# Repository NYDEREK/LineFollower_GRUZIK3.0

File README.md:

<h1 align="center">GRUZIK3.0: Line Follower Robot</h1>

<div align="center">

<i>Loved the project? Please consider giving a Star ⭐️</i>

</div>

> **GRUZIK2.0 is a lightweight construction (69g) designed for the "Line Follower Light" competition. The robot features Bluetooth communication with a smartphone app and uses a digital sensor instead of analog.**

> **here is a quick video of current progres with GRUZIK3.0 - https://www.youtube.com/watch?v=DpuIcFJMwbQ**
<div align="center">
  
</div>

## Hardware

> **The simple lightweight construction (69g) allows the robot to achieve high speed on the track.**
> **PCBs were designed in KiCAD 8.0 and manufactured by JLCPCB. The rims were 3D printed with PLA for Kyosho "Mini Z" tires.**
> **The light dualsky 150mAh battery provides enough current (max 30C) without adding too much weight (10g).**
> **The Pololu 2211 motor (10:1) with max current 1.6A per one requires the use of two separate TB6612FNG motor drivers with connected channels (max 2A per driver).**
> **The HC-05 Bluetooth module gives communication range up to 10m.**
> **The fast ARM microcontroller STM32G474RET6 (max 170MHz) provides a lot of software capabilities.**

- uC - STM32G474RET6
- drivers - TB6612FNG
- sensor - 12x KTIR0711S
- battery - 150mAh LiPo dualsky
- wheels - Kyosho Mini Z
- motors - Pololu 3071 HPCB
- Bluetooth - HC-04
- Encoders - AMS AS5047P-ATSM
- IMU - MPU-6050

## 🗺️ Mapping 🗺️
> **GRUZIK3.0 is able to record it's route and save it on uSD card. Results can be represented as XY map and optimized by Python algorithm, robot is able to recreate optimized map in real world achieving max speed for the given route**

<div align="center">

</div>

## 📱Bluetooth Apps 📱

> **Thease are simple Bluetooth apps created with MIT App Inventor. Spps start and stop the robot. The Modes pad is responsible for quickly adapting the speed and accuracy of the robot to the route using modes, and the application also displays the battery charge status. Second app is mainly for tweaking PID settings it allows you to change any parameter in seconds**

<div align="center">

</div>

## What I have learned 
> **This project wasn't easy but I learned a lot new things in software and hardware. I had a lot of failures during this project but I have never gave up and always kept pushing my own limits.**

- I mastered PID controll
 
- IMU implemantation 
 
- Encoder implementation with PI speed regulator on motors
 
- Mapping and optimizing Paths

- Improved my PCB design skills (KiCAD)

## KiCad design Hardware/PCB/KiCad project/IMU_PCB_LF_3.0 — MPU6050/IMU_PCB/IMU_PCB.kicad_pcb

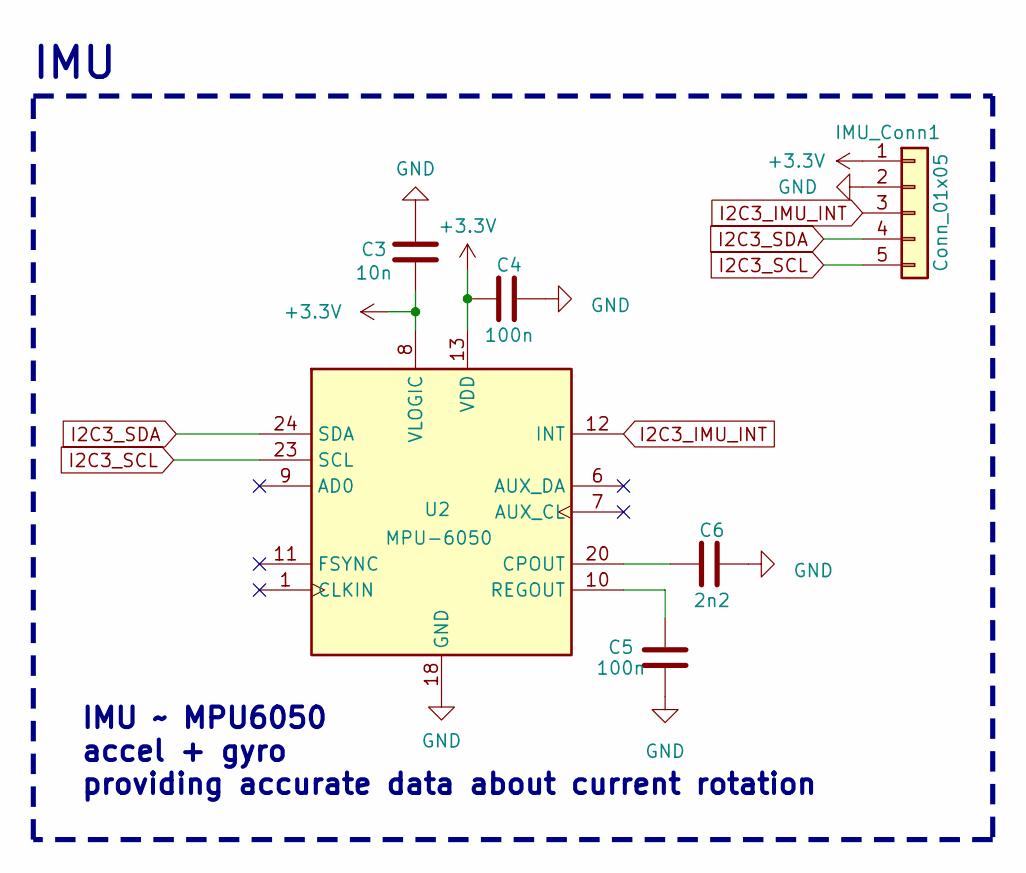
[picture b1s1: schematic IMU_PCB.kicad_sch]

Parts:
C3: 10n; C_0603_1608Metric
C4, C5: 100n; C_0603_1608Metric
C6: 2n2; C_0603_1608Metric
IMU_Conn1: Conn_01x05; IMU_conn
U2: MPU-6050; InvenSense_QFN-24_4x4mm_P0.5mm

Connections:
+3.3V: C3.1, C4.2, IMU_Conn1.1, U2.8 (VLOGIC), U2.13 (VDD)
GND: C3.2, C4.1, C5.2, C6.1, IMU_Conn1.2, U2.18 (GND)
I2C3_IMU_INT: IMU_Conn1.3, U2.12 (INT)
I2C3_SCL: IMU_Conn1.5, U2.23 (SCL)
I2C3_SDA: IMU_Conn1.4, U2.24 (SDA)
unnamed: C6.2, U2.20 (CPOUT)
unnamed: C5.1, U2.10 (REGOUT)

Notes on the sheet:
IMU
IMU ~ MPU6050 accel + gyro providing accurate data about current rotation

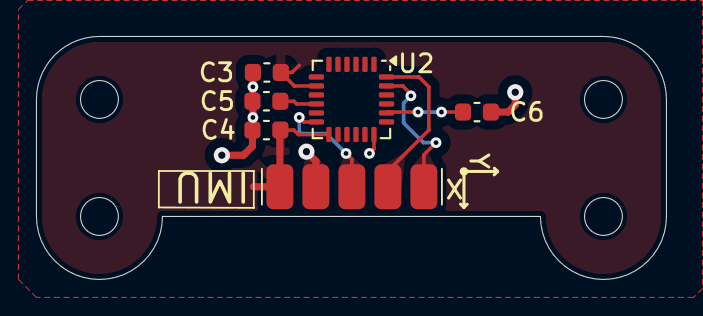
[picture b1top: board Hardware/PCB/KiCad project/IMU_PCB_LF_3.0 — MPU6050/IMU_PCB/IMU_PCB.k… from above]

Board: 2 copper layers, 35.0 x 13.5 mm, 6 parts (0 on the bottom side), 7 nets.

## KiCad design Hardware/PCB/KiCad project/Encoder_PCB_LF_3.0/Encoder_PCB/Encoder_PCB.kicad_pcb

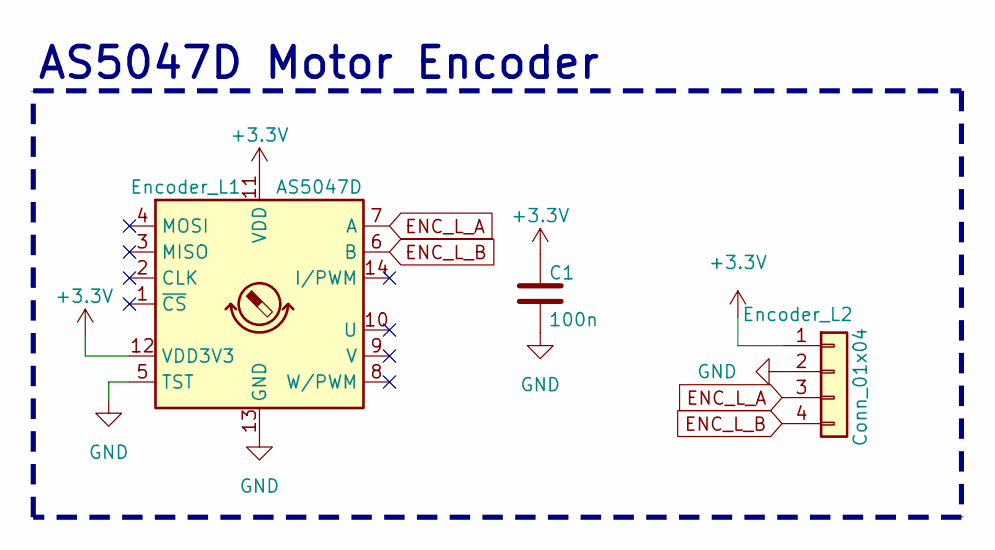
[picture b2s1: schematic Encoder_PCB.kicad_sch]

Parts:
C1: 100n; C_0603_1608Metric
Encoder_L1: AS5047D; TSSOP-14_4.4x5mm_P0.65mm
Encoder_L2: Conn_01x04; Encoder_short_conn

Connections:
+3.3V: C1.1, Encoder_L1.11 (VDD), Encoder_L1.12 (VDD3V3), Encoder_L2.1
ENC_L_A: Encoder_L1.7 (A), Encoder_L2.3
ENC_L_B: Encoder_L1.6 (B), Encoder_L2.4
GND: C1.2, Encoder_L1.5 (TST), Encoder_L1.13 (GND), Encoder_L2.2

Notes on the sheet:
AS5047D Motor Encoder

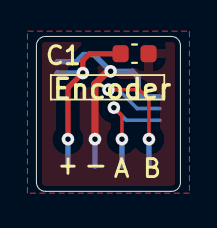
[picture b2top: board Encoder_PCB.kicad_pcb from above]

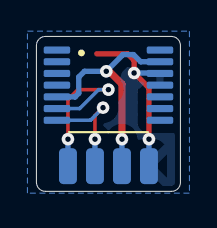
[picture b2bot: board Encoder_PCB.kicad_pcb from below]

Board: 2 copper layers, 8.0 x 8.6 mm, 3 parts (2 on the bottom side), 4 nets.

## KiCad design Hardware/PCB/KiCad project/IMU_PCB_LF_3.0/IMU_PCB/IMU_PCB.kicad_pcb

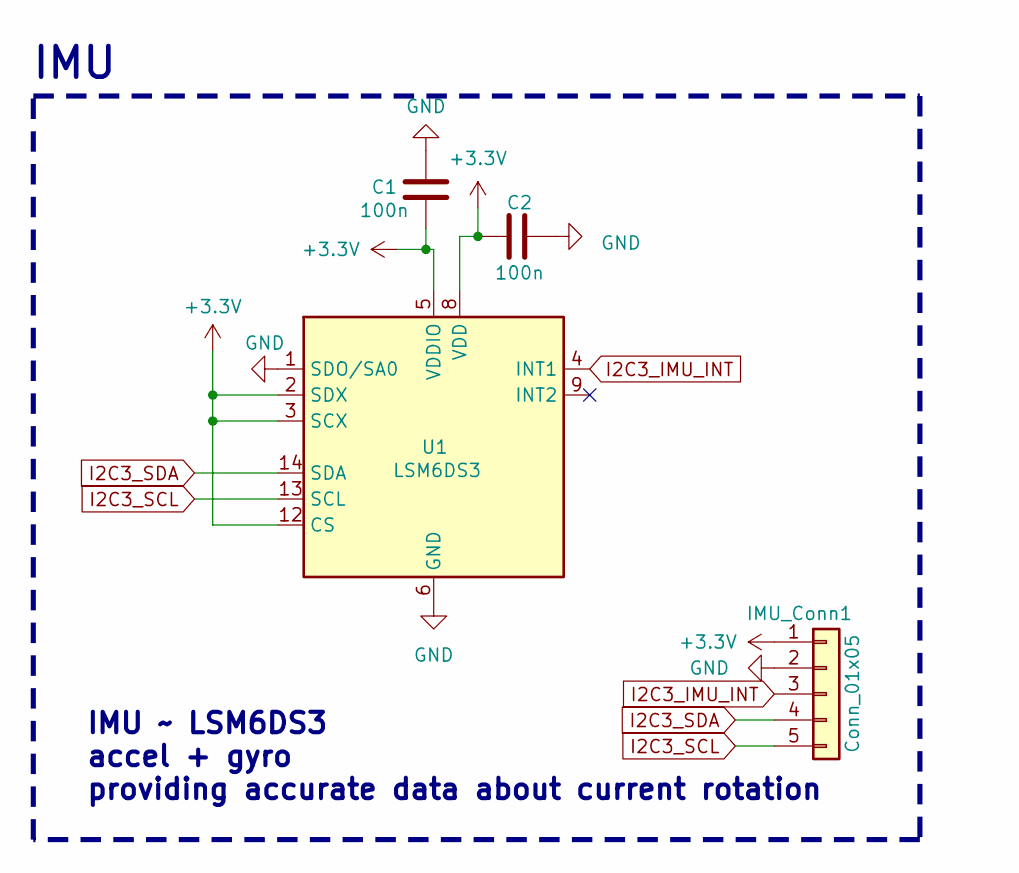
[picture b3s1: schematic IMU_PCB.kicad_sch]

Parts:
C1, C2: 100n; C_0603_1608Metric
IMU_Conn1: Conn_01x05; IMU_conn
U1: LSM6DS3; LGA-14_3x2.5mm_P0.5mm_LayoutBorder3x4y

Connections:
+3.3V: C1.1, C2.2, IMU_Conn1.1, U1.2 (SDX), U1.3 (SCX), U1.5 (VDDIO), U1.8 (VDD), U1.12 (CS)
GND: C1.2, C2.1, IMU_Conn1.2, U1.1 (SDO/SA0), U1.6 (GND), U1.7 (GND)
I2C3_IMU_INT: IMU_Conn1.3, U1.4 (INT1)
I2C3_SCL: IMU_Conn1.5, U1.13 (SCL)
I2C3_SDA: IMU_Conn1.4, U1.14 (SDA)

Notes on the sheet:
IMU ~ LSM6DS3 accel + gyro providing accurate data about current rotation
IMU

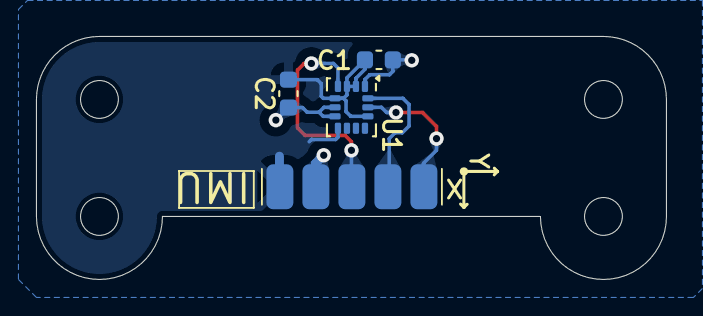
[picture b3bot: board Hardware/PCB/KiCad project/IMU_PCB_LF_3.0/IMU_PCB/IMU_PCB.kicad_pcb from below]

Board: 2 copper layers, 35.0 x 13.5 mm, 4 parts (4 on the bottom side), 5 nets.

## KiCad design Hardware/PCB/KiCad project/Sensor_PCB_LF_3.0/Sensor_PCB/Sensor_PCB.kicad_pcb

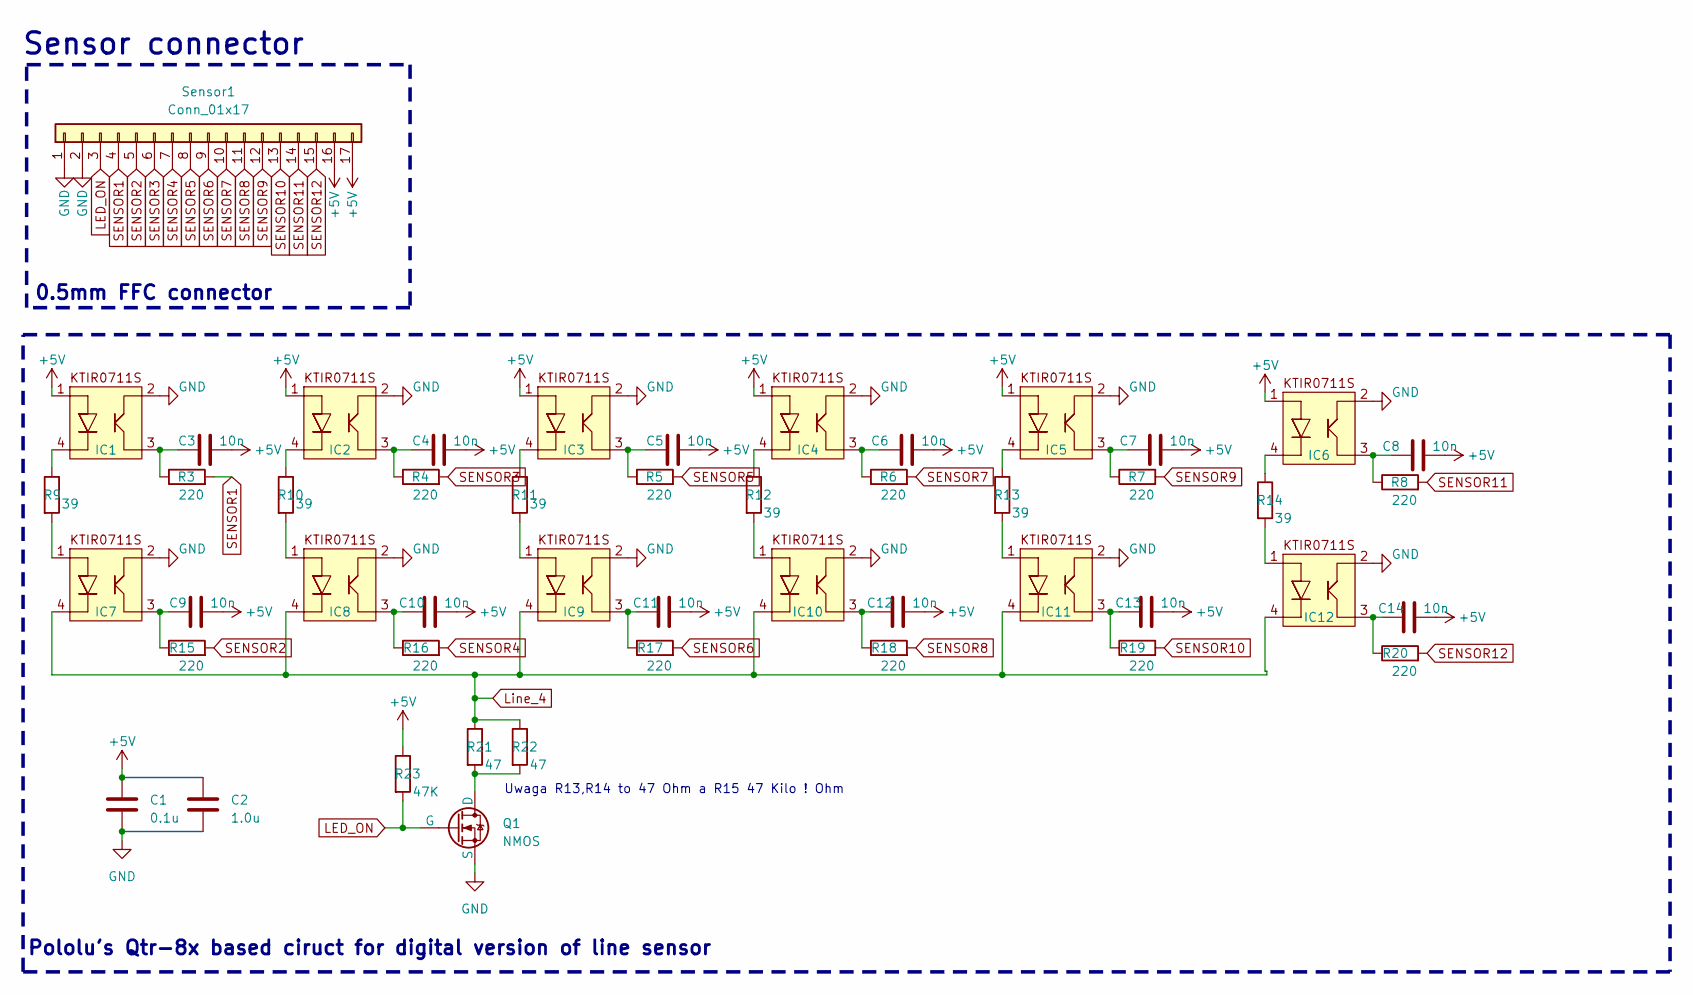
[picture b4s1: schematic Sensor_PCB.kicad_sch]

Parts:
C1: 0.1u; C_0603_1608Metric
C2: 1.0u; C_0603_1608Metric
C3, C4, C5, C6, C7, C8, C9, C10, C11, C12, C13, C14: 10n; C_0603_1608Metric
IC1, IC2, IC3, IC4, IC5, IC6, IC7, IC8, IC9, IC10, IC11, IC12: KTIR0711S
Q1: NMOS; NMOS_SN
R3, R4, R5, R6, R7, R8, R15, R16, R17, R18, R19, R20: 220; R_0603_1608Metric
R9, R10, R11, R12, R13, R14: 39; R_0603_1608Metric
R21, R22: 47; R_0603_1608Metric
R23: 47K; R_0603_1608Metric
Sensor1: Conn_01x17; Hirose_FH12-17S-0.5SH_1x17-1MP_P0.50mm_Horizontal

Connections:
+5V: C1.1, C2.1, C3.2, C4.2, C5.2, C6.2, C7.2, C8.2, C9.2, C10.2, C11.2, C12.2, C13.2, C14.2, IC1.1, IC2.1, IC3.1, IC4.1, IC5.1, IC6.1, R23.1, Sensor1.16, Sensor1.17; also elsewhere on the board
GND: C1.2, C2.2, IC1.2, IC2.2, IC3.2, IC4.2, IC5.2, IC6.2, IC7.2, IC8.2, IC9.2, IC10.2, IC11.2, IC12.2, Q1.3 (S), Sensor1.1, Sensor1.2; also elsewhere on the board
LED_ON: Q1.2 (G), R23.2, Sensor1.3; also elsewhere on the board
Line_4: IC7.4, IC8.4, IC9.4, IC10.4, IC11.4, IC12.4, R21.1, R22.1
unnamed: C3.1, IC1.3, R3.1
unnamed: C4.1, IC2.3, R4.1
unnamed: C5.1, IC3.3, R5.1
unnamed: C6.1, IC4.3, R6.1
unnamed: C7.1, IC5.3, R7.1
unnamed: C8.1, IC6.3, R8.1
unnamed: C9.1, IC7.3, R15.1
unnamed: C10.1, IC8.3, R16.1
unnamed: C11.1, IC9.3, R17.1
unnamed: C12.1, IC10.3, R18.1
unnamed: C13.1, IC11.3, R19.1
unnamed: C14.1, IC12.3, R20.1
unnamed: IC1.4, R9.1
unnamed: IC2.4, R10.1
unnamed: IC3.4, R11.1
unnamed: IC4.4, R12.1
unnamed: IC5.4, R13.1
unnamed: IC6.4, R14.1
unnamed: IC7.1, R9.2
unnamed: IC8.1, R10.2
unnamed: IC9.1, R11.2
unnamed: IC10.1, R12.2
unnamed: IC11.1, R13.2
unnamed: IC12.1, R14.2
unnamed: Q1.1 (D), R21.2, R22.2
SENSOR1: R3.2, Sensor1.4; also elsewhere on the board
SENSOR2: R15.2, Sensor1.5; also elsewhere on the board
SENSOR3: R4.2, Sensor1.6; also elsewhere on the board
SENSOR4: R16.2, Sensor1.7; also elsewhere on the board
SENSOR5: R5.2, Sensor1.8; also elsewhere on the board
SENSOR6: R17.2, Sensor1.9; also elsewhere on the board
SENSOR7: R6.2, Sensor1.10; also elsewhere on the board
SENSOR8: R18.2, Sensor1.11; also elsewhere on the board
SENSOR9: R7.2, Sensor1.12; also elsewhere on the board
SENSOR10: R19.2, Sensor1.13; also elsewhere on the board
SENSOR11: R8.2, Sensor1.14; also elsewhere on the board
SENSOR12: R20.2, Sensor1.15; also elsewhere on the board

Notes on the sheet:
Uwaga R13,R14 to 47 Ohm a R15 47 Kilo ! Ohm
Pololu's Qtr-8x based ciruct for digital version of line sensor
0.5mm FFC connector
Sensor connector

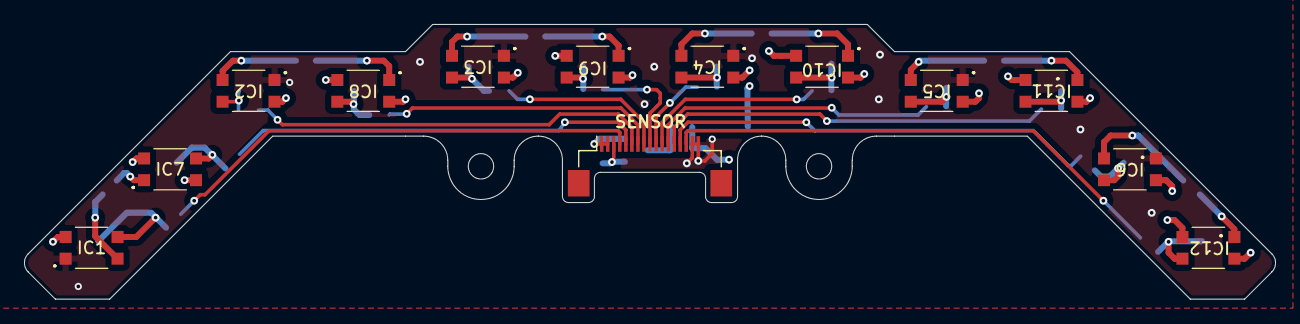
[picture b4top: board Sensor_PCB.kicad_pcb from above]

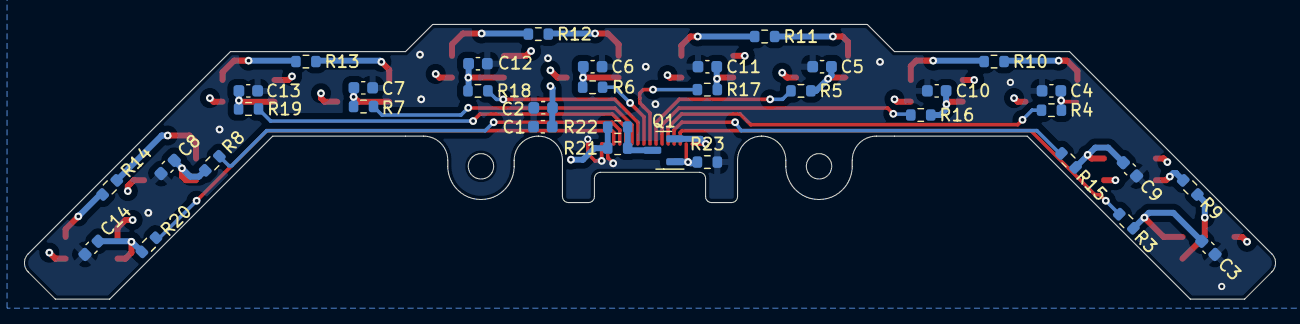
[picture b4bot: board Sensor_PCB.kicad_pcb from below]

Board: 4 copper layers, 103.6 x 22.8 mm, 49 parts (36 on the bottom side), 41 nets.

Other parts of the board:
SENSOR: Conn_01x17; Hirose_FH12-17S-0.5SH_1x17-1MP_P0.50mm_Horizontal

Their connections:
+5V: SENSOR.16, SENSOR.17; also elsewhere on the board
GND: SENSOR.1, SENSOR.2; also elsewhere on the board
LED_ON: SENSOR.3; also elsewhere on the board
SENSOR1: SENSOR.4; also elsewhere on the board
SENSOR2: SENSOR.5; also elsewhere on the board
SENSOR3: SENSOR.6; also elsewhere on the board
SENSOR4: SENSOR.7; also elsewhere on the board
SENSOR5: SENSOR.8; also elsewhere on the board
SENSOR6: SENSOR.9; also elsewhere on the board
SENSOR7: SENSOR.10; also elsewhere on the board
SENSOR8: SENSOR.11; also elsewhere on the board
SENSOR9: SENSOR.12; also elsewhere on the board
SENSOR10: SENSOR.13; also elsewhere on the board
SENSOR11: SENSOR.14; also elsewhere on the board
SENSOR12: SENSOR.15; also elsewhere on the board

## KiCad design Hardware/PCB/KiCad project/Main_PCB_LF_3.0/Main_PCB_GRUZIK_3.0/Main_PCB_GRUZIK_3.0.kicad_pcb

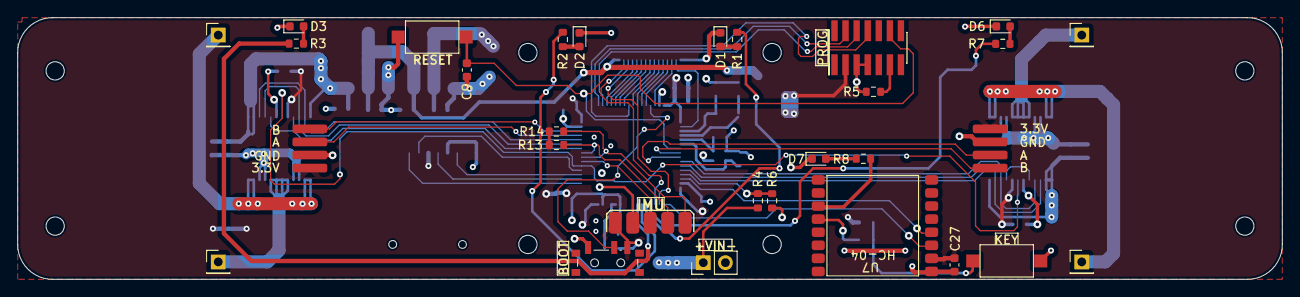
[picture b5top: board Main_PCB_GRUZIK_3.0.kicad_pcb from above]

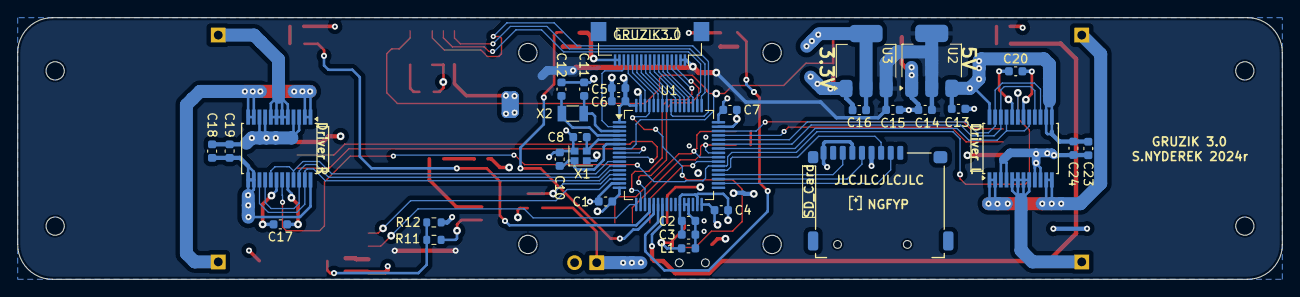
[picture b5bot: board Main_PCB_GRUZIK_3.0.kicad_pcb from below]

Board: 4 copper layers, 145.0 x 30.0 mm, 63 parts (33 on the bottom side), 65 nets.

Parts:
+VIN-: +VIN-; PinHeader_1x02_P2.54mm_Vertical
BOOT: SW_DPDT_x2; SW_SPDT_PCM12
C1, C2, C5, C6, C7, C9, C17, C18, C20, C23: 100n; C_0603_1608Metric
C3, C27: 1u; C_0603_1608Metric
C4: 4u7; C_0603_1608Metric
C8, C10: 6p8; C_0603_1608Metric
C11, C12: 5p1; C_0603_1608Metric
C13, C14, C15, C16, C19, C24: 10u; C_0603_1608Metric
D1, D2, D3, D6: BLUE; LED_0603_1608Metric
D7: Green; LED_0603_1608Metric
Driver L: TB6612FNG; SSOP-24_5.3x8.2mm_P0.65mm
Driver R: TB6612FNG; SSOP-24_5.3x8.2mm_P0.65mm
Encoder_L1, Encoder_L2: Conn_01x04; Encoder_short_conn
GRUZIK3.0: Conn_01x17; Hirose_FH12-17S-0.5SH_1x17-1MP_P0.50mm_Horizontal
IMU: Conn_01x05; IMU_conn
KEY: SW_SPST; SW_SPST_CK_RS282G05A3
L1: 27n; L_0603_1608Metric
P1, P2, P3, P4: Conn_01x01; PinHeader_1x01_P2.54mm_Vertical
PROG: Conn_02x07_Odd_Even; PinHeader_2x07_P1.27mm_Vertical_SMD
R1, R2, R3, R7: 510R; R_0603_1608Metric
R4: 330K; R_0603_1608Metric
R5: 100R; R_0603_1608Metric
R6: 200K; R_0603_1608Metric
R8: 510; R_0603_1608Metric
R11: 220; R_0603_1608Metric
R12, R13, R14: 10K; R_0603_1608Metric
RESET: SW_SPST; SW_SPST_CK_RS282G05A3
SD_Card: Micro_SD_Card; micro_SD
U1: STM32G474RETx; LQFP-64_10x10mm_P0.5mm
U2: AMS1117-5.0; SOT-223-3_TabPin2
U3: AMS1117-3.3; SOT-223-3_TabPin2
U7: HC-04
X1: 24Mhz; Crystal_SMD_2016-4Pin_2.0x1.6mm
X2: 32.768KHz; Crystal_SMD_3215-2Pin_3.2x1.5mm

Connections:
+3V3: BOOT.3 (C), C1.1, C4.1, C5.1, C6.1, C7.1, C16.1, C17.1, C20.1, C27.1, Driver L.20 (VCC), Driver R.20 (VCC), Encoder_L1.1, Encoder_L2.1, IMU.1, L1.2, PROG.3, R12.2, R13.1, R14.1, SD_Card.4 (VDD), U1.1 (VBAT), U1.16 (VDD), U1.32 (VDD), U1.48 (VDD), U1.64 (VDD), U3.2 (VO), U7.2 (3.3V)
+5V: C14.1, C15.1, GRUZIK3.0.1, GRUZIK3.0.2, U2.2 (VO), U3.3 (VI)
/HSE_IN: C8.2, U1.5 (PF0), X1.3
/HSE_OUT: C10.2, U1.6 (PF1), X1.1
/LSE_IN: C11.2, U1.3 (PC14), X2.2
/LSE_OUT: C12.2, U1.4 (PC15), X2.1
ADC_IN2: R4.1, R6.2, U1.13 (PA1)
BOOT0: BOOT.2 (B), U1.61 (PB8)
ENC_L_A: Encoder_L1.3, U1.45 (PA11)
ENC_L_B: Encoder_L1.4, U1.46 (PA12)
ENC_R_A: Encoder_L2.3, U1.9 (PC1)
ENC_R_B: Encoder_L2.4, U1.8 (PC0)
GND: +VIN-.2, BOOT.1 (A), C1.2, C2.2, C3.2, C4.2, C5.2, C6.2, C7.2, C8.1, C9.1, C10.1, C11.1, C12.1, C13.2, C14.2, C15.2, C16.2, C17.2, C18.2, C19.2, C20.2, C23.2, C24.2, C27.2, D1.1 (K), D2.1 (K), D3.1 (K), D6.1 (K), D7.1 (K), Driver L.3 (PGND1), Driver L.4 (PGND1), Driver L.9 (PGND2), Driver L.10 (PGND2), Driver L.18 (GND), Driver R.3 (PGND1), Driver R.4 (PGND1), Driver R.9 (PGND2), Driver R.10 (PGND2), Driver R.18 (GND), Encoder_L1.2, Encoder_L2.2, GRUZIK3.0.16, GRUZIK3.0.17, IMU.2, KEY.2 (B), PROG.5, PROG.7, R5.1, R6.1, RESET.1 (A), SD_Card.6 (VSS), SD_Card.9 (SHIELD), U1.15 (VSS), U1.27 (VSSA), U1.31 (VSS), U1.47 (VSS), U1.63 (VSS), U2.1 (GND), U3.1 (GND), U7.1 (GND), X1.2, X1.4
I2C3_IMU_INT: IMU.3, U1.39 (PC7)
I2C3_SCL: IMU.5, R14.2, U1.40 (PC8)
I2C3_SDA: IMU.4, R13.2, U1.41 (PC9)
LED_1: R3.2, U1.23 (PC5)
LED_2: R2.2, U1.22 (PC4)
LED_3: R1.2, U1.21 (PA7)
LED_4: R7.2, U1.20 (PA6)
LED_ON: GRUZIK3.0.15, U1.2 (PC13)
LPUART1_RX: U1.17 (PA3), U7.3 (Tx)
LPUART1_TX: U1.14 (PA2), U7.4 (Rx)
Motor_L_A: Driver L.17 (BIN1), Driver L.21 (AIN1), U1.42 (PA8)
Motor_L_B: Driver L.16 (BIN2), Driver L.22 (AIN2), U1.43 (PA9)
Motor_R_A: Driver R.17 (BIN1), Driver R.21 (AIN1), U1.10 (PC2)
Motor_R_B: Driver R.16 (BIN2), Driver R.22 (AIN2), U1.11 (PC3)
Motor_STBY: Driver L.19 (STBY), Driver R.19 (STBY), U1.38 (PC6)
NRST: C9.2, PROG.12, RESET.2 (B), U1.7 (PG10)
unnamed: D1.2 (A), R1.1
unnamed: D2.2 (A), R2.1
unnamed: D3.2 (A), R3.1
unnamed: D6.2 (A), R7.1
unnamed: D7.2 (A), R8.2
unnamed: KEY.1 (A), R11.2, R12.1
unnamed: Driver R.5 (AO2), Driver R.6 (AO2), Driver R.7 (BO2), Driver R.8 (BO2), P1.1
unnamed: Driver R.1 (AO1), Driver R.2 (AO1), Driver R.11 (BO1), Driver R.12 (BO1), P2.1
unnamed: Driver L.5 (AO2), Driver L.6 (AO2), Driver L.7 (BO2), Driver L.8 (BO2), P3.1
unnamed: Driver L.1 (AO1), Driver L.2 (AO1), Driver L.11 (BO1), Driver L.12 (BO1), P4.1
unnamed: PROG.11, R5.2
unnamed: R11.1, U7.12 (KEY)
unnamed: R8.1, U7.11 (LED)
PWM_L: Driver L.15 (PWMB), Driver L.23 (PWMA), U1.44 (PA10)
PWM_R: Driver R.15 (PWMB), Driver R.23 (PWMA), U1.12 (PA0)
SENSOR1: GRUZIK3.0.14, U1.62 (PB9)
SENSOR2: GRUZIK3.0.13, U1.60 (PB7)
SENSOR3: GRUZIK3.0.12, U1.59 (PB6)
SENSOR4: GRUZIK3.0.11, U1.58 (PB5)
SENSOR5: GRUZIK3.0.10, U1.57 (PB4)
SENSOR6: GRUZIK3.0.9, U1.55 (PD2)
SENSOR7: GRUZIK3.0.8, U1.54 (PC12)
SENSOR8: GRUZIK3.0.7, U1.53 (PC11)
SENSOR9: GRUZIK3.0.6, U1.52 (PC10)
SENSOR10: GRUZIK3.0.5, U1.51 (PA15)
SENSOR11: GRUZIK3.0.4, U1.18 (PA4)
SENSOR12: GRUZIK3.0.3, U1.19 (PA5)
SPI2_CLK: SD_Card.5 (CLK), U1.35 (PB13)
SPI2_CS: SD_Card.2 (DAT3/CD), U1.34 (PB12)
SPI2_MISO: SD_Card.7 (DAT0), U1.36 (PB14)
SPI2_MOSI: SD_Card.3 (CMD), U1.37 (PB15)
SYS_JTCK_SWCLK: PROG.6, U1.50 (PA14)
SYS_JTDO_SWO: PROG.8, U1.56 (PB3)
SYS_JTMS_SWDIO: PROG.4, U1.49 (PA13)
VDC: +VIN-.1, C13.1, C18.1, C19.1, C23.1, C24.1, Driver L.13 (VM2), Driver L.14 (VM3), Driver L.24 (VM1), Driver R.13 (VM2), Driver R.14 (VM3), Driver R.24 (VM1), R4.2, U2.3 (VI)
VREF+: C2.1, C3.1, L1.1, U1.28 (VREF+), U1.29 (VDDA)

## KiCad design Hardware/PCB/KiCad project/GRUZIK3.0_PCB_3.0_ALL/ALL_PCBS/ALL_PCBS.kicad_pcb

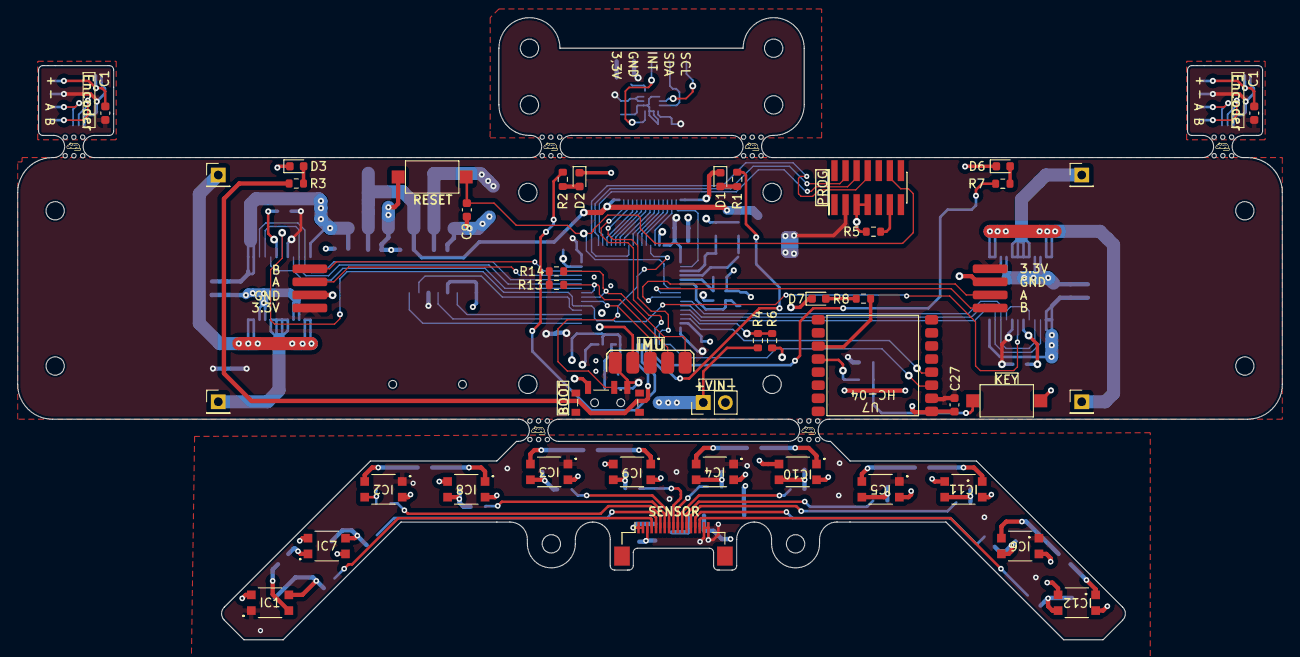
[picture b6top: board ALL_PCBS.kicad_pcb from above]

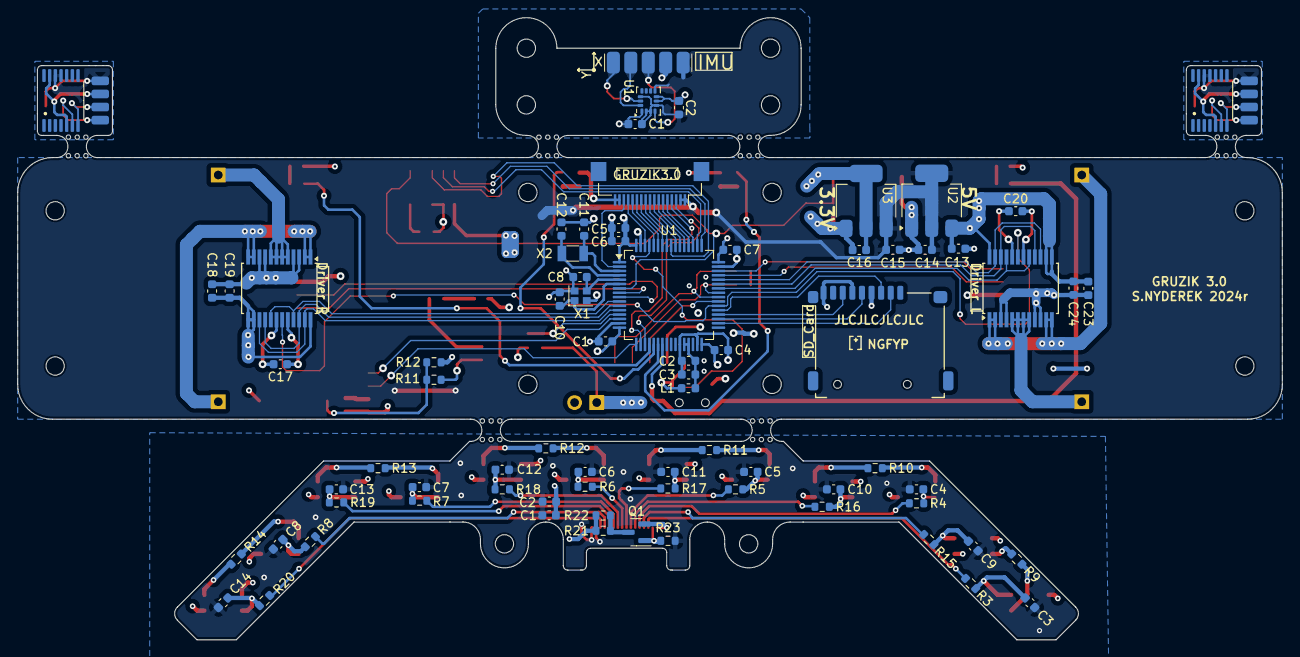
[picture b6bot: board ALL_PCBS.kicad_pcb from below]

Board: 4 copper layers, 145.0 x 71.3 mm, 128 parts (77 on the bottom side), 92 nets.

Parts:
+VIN-: +VIN-; PinHeader_1x02_P2.54mm_Vertical
BOOT: SW_DPDT_x2; SW_SPDT_PCM12
C1, C1#2, C1#3, C1#4, C2, C2#2, C5, C6#2, C7#2, C9, C17, C18, C20, C23: 100n; C_0603_1608Metric
C1#5: 0.1u; C_0603_1608Metric
C2#3: 1.0u; C_0603_1608Metric
C3, C27: 1u; C_0603_1608Metric
C3#2, C4, C5#2, C6, C7, C8, C9#2, C10#2, C11#2, C12, C13, C14: 10n; C_0603_1608Metric
C4#2: 4u7; C_0603_1608Metric
C8#2, C10: 6p8; C_0603_1608Metric
C11, C12#2: 5p1; C_0603_1608Metric
C13#2, C14#2, C15, C16, C19, C24: 10u; C_0603_1608Metric
D1, D2, D3, D6: BLUE; LED_0603_1608Metric
D7: Green; LED_0603_1608Metric
Driver L: TB6612FNG; SSOP-24_5.3x8.2mm_P0.65mm
Driver R: TB6612FNG; SSOP-24_5.3x8.2mm_P0.65mm
Encoder_L1, Encoder_L2, Encoder_L2#2, Encoder_L2#3: Conn_01x04; Encoder_short_conn
Encoder_L1#2, Encoder_L1#3: AS5047D; TSSOP-14_4.4x5mm_P0.65mm
GRUZIK3.0: Conn_01x17; Hirose_FH12-17S-0.5SH_1x17-1MP_P0.50mm_Horizontal
IC1, IC2, IC3, IC4, IC5, IC6, IC7, IC8, IC9, IC10, IC11, IC12: KTIR0711S
IMU: Conn_01x05; IMU_conn
IMU_Conn1: Conn_01x05; IMU_conn
KEY: SW_SPST; SW_SPST_CK_RS282G05A3
L1: 27n; L_0603_1608Metric
P1, P2, P3, P4: Conn_01x01; PinHeader_1x01_P2.54mm_Vertical
PROG: Conn_02x07_Odd_Even; PinHeader_2x07_P1.27mm_Vertical_SMD
Q1: NMOS; NMOS_SN
R1, R2, R3, R7: 510R; R_0603_1608Metric
R3#2, R4#2, R5#2, R6#2, R7#2, R8#2, R11#2, R15, R16, R17, R18, R19, R20: 220; R_0603_1608Metric
R4: 330K; R_0603_1608Metric
R5: 100R; R_0603_1608Metric
R6: 200K; R_0603_1608Metric
R8: 510; R_0603_1608Metric
R9, R10, R11, R12#2, R13#2, R14#2: 39; R_0603_1608Metric
R12, R13, R14: 10K; R_0603_1608Metric
R21, R22: 47; R_0603_1608Metric
R23: 47K; R_0603_1608Metric
RESET: SW_SPST; SW_SPST_CK_RS282G05A3
SD_Card: Micro_SD_Card; micro_SD
SENSOR: Conn_01x17; Hirose_FH12-17S-0.5SH_1x17-1MP_P0.50mm_Horizontal
U1: LSM6DS3; LGA-14_3x2.5mm_P0.5mm_LayoutBorder3x4y
U1#2: STM32G474RETx; LQFP-64_10x10mm_P0.5mm
U2: AMS1117-5.0; SOT-223-3_TabPin2
U3: AMS1117-3.3; SOT-223-3_TabPin2
U7: HC-04
X1: 24Mhz; Crystal_SMD_2016-4Pin_2.0x1.6mm
X2: 32.768KHz; Crystal_SMD_3215-2Pin_3.2x1.5mm
mouse-bite-2.54mm-4.66mm, mouse-bite-2.54mm-4.66mm#2, mouse-bite-2.54mm-4.66mm#3, mouse-bite-2.54mm-4.66mm#4, mouse-bite-2.54mm-4.66mm#5, mouse-bite-2.54mm-4.66mm#6: VAL**; mouse-bite-2.54mm-4.66mm

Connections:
+3.3V: C1.1, C1#2.1, C1#3.1, C2#2.2, Encoder_L1#2.11 (VDD), Encoder_L1#2.12 (VDD3V3), Encoder_L1#3.11 (VDD), Encoder_L1#3.12 (VDD3V3), Encoder_L2#2.1, Encoder_L2#3.1, IMU_Conn1.1, U1.2 (SDX), U1.3 (SCX), U1.5 (VDDIO), U1.8 (VDD), U1.12 (CS)
+3V3: BOOT.3 (C), C1#4.1, C4#2.1, C5.1, C6#2.1, C7#2.1, C16.1, C17.1, C20.1, C27.1, Driver L.20 (VCC), Driver R.20 (VCC), Encoder_L1.1, Encoder_L2.1, IMU.1, L1.2, PROG.3, R12.2, R13.1, R14.1, SD_Card.4 (VDD), U1#2.1 (VBAT), U1#2.16 (VDD), U1#2.32 (VDD), U1#2.48 (VDD), U1#2.64 (VDD), U3.2 (VO), U7.2 (3.3V)
+5V: C1#5.1, C2#3.1, C3#2.2, C4.2, C5#2.2, C6.2, C7.2, C8.2, C9#2.2, C10#2.2, C11#2.2, C12.2, C13.2, C14.2, C14#2.1, C15.1, GRUZIK3.0.1, GRUZIK3.0.2, IC1.1, IC2.1, IC3.1, IC4.1, IC5.1, IC6.1, R23.1, SENSOR.16, SENSOR.17, U2.2 (VO), U3.3 (VI)
/HSE_IN: C8#2.2, U1#2.5 (PF0), X1.3
/HSE_OUT: C10.2, U1#2.6 (PF1), X1.1
/LSE_IN: C11.2, U1#2.3 (PC14), X2.2
/LSE_OUT: C12#2.2, U1#2.4 (PC15), X2.1
ADC_IN2: R4.1, R6.2, U1#2.13 (PA1)
BOOT0: BOOT.2 (B), U1#2.61 (PB8)
ENC_L_A: Encoder_L1.3, Encoder_L1#2.7 (A), Encoder_L1#3.7 (A), Encoder_L2#2.3, Encoder_L2#3.3, U1#2.45 (PA11)
ENC_L_B: Encoder_L1.4, Encoder_L1#2.6 (B), Encoder_L1#3.6 (B), Encoder_L2#2.4, Encoder_L2#3.4, U1#2.46 (PA12)
ENC_R_A: Encoder_L2.3, U1#2.9 (PC1)
ENC_R_B: Encoder_L2.4, U1#2.8 (PC0)
GND: +VIN-.2, BOOT.1 (A), C1.2, C1#2.2, C1#3.2, C1#4.2, C1#5.2, C2.2, C2#2.1, C2#3.2, C3.2, C4#2.2, C5.2, C6#2.2, C7#2.2, C8#2.1, C9.1, C10.1, C11.1, C12#2.1, C13#2.2, C14#2.2, C15.2, C16.2, C17.2, C18.2, C19.2, C20.2, C23.2, C24.2, C27.2, D1.1 (K), D2.1 (K), D3.1 (K), D6.1 (K), D7.1 (K), Driver L.3 (PGND1), Driver L.4 (PGND1), Driver L.9 (PGND2), Driver L.10 (PGND2), Driver L.18 (GND), Driver R.3 (PGND1), Driver R.4 (PGND1), Driver R.9 (PGND2), Driver R.10 (PGND2), Driver R.18 (GND), Encoder_L1.2, Encoder_L1#2.5 (TST), Encoder_L1#2.13 (GND), Encoder_L1#3.5 (TST), Encoder_L1#3.13 (GND), Encoder_L2.2, Encoder_L2#2.2, Encoder_L2#3.2, GRUZIK3.0.16, GRUZIK3.0.17, IC1.2, IC2.2, IC3.2, IC4.2, IC5.2, IC6.2, IC7.2, IC8.2, IC9.2, IC10.2, IC11.2, IC12.2, IMU.2, IMU_Conn1.2, KEY.2 (B), PROG.5, PROG.7, Q1.3 (S), R5.1, R6.1, RESET.1 (A), SD_Card.6 (VSS), SD_Card.9 (SHIELD), SENSOR.1, SENSOR.2, U1.1 (SDO/SA0), U1.6 (GND), U1.7 (GND), U1#2.15 (VSS), U1#2.27 (VSSA), U1#2.31 (VSS), U1#2.47 (VSS), U1#2.63 (VSS), U2.1 (GND), U3.1 (GND), U7.1 (GND), X1.2, X1.4
I2C3_IMU_INT: IMU.3, IMU_Conn1.3, U1.4 (INT1), U1#2.39 (PC7)
I2C3_SCL: IMU.5, IMU_Conn1.5, R14.2, U1.13 (SCL), U1#2.40 (PC8)
I2C3_SDA: IMU.4, IMU_Conn1.4, R13.2, U1.14 (SDA), U1#2.41 (PC9)
LED_1: R3.2, U1#2.23 (PC5)
LED_2: R2.2, U1#2.22 (PC4)
LED_3: R1.2, U1#2.21 (PA7)
LED_4: R7.2, U1#2.20 (PA6)
LED_ON: GRUZIK3.0.15, Q1.2 (G), R23.2, SENSOR.3, U1#2.2 (PC13)
LPUART1_RX: U1#2.17 (PA3), U7.3 (Tx)
LPUART1_TX: U1#2.14 (PA2), U7.4 (Rx)
Line_4: IC7.4, IC8.4, IC9.4, IC10.4, IC11.4, IC12.4, R21.1, R22.1
Motor_L_A: Driver L.17 (BIN1), Driver L.21 (AIN1), U1#2.42 (PA8)
Motor_L_B: Driver L.16 (BIN2), Driver L.22 (AIN2), U1#2.43 (PA9)
Motor_R_A: Driver R.17 (BIN1), Driver R.21 (AIN1), U1#2.10 (PC2)
Motor_R_B: Driver R.16 (BIN2), Driver R.22 (AIN2), U1#2.11 (PC3)
Motor_STBY: Driver L.19 (STBY), Driver R.19 (STBY), U1#2.38 (PC6)
NRST: C9.2, PROG.12, RESET.2 (B), U1#2.7 (PG10)
unnamed: C3#2.1, IC1.3, R3#2.1
unnamed: C4.1, IC2.3, R4#2.1
unnamed: C5#2.1, IC3.3, R5#2.1
unnamed: C6.1, IC4.3, R6#2.1
unnamed: C7.1, IC5.3, R7#2.1
unnamed: C8.1, IC6.3, R8#2.1
unnamed: C9#2.1, IC7.3, R15.1
unnamed: C10#2.1, IC8.3, R16.1
unnamed: C11#2.1, IC9.3, R17.1
unnamed: C12.1, IC10.3, R18.1
unnamed: C13.1, IC11.3, R19.1
unnamed: C14.1, IC12.3, R20.1
unnamed: D1.2 (A), R1.1
unnamed: D2.2 (A), R2.1
unnamed: D3.2 (A), R3.1
unnamed: D6.2 (A), R7.1
unnamed: D7.2 (A), R8.2
unnamed: IC1.4, R9.1
unnamed: IC2.4, R10.1
unnamed: IC3.4, R11.1
unnamed: IC4.4, R12#2.1
unnamed: IC5.4, R13#2.1
unnamed: IC6.4, R14#2.1
unnamed: IC7.1, R9.2
unnamed: IC8.1, R10.2
unnamed: IC9.1, R11.2
unnamed: IC10.1, R12#2.2
unnamed: IC11.1, R13#2.2
unnamed: IC12.1, R14#2.2
unnamed: KEY.1 (A), R11#2.2, R12.1
unnamed: Driver R.5 (AO2), Driver R.6 (AO2), Driver R.7 (BO2), Driver R.8 (BO2), P1.1
unnamed: Driver R.1 (AO1), Driver R.2 (AO1), Driver R.11 (BO1), Driver R.12 (BO1), P2.1
unnamed: Driver L.5 (AO2), Driver L.6 (AO2), Driver L.7 (BO2), Driver L.8 (BO2), P3.1
unnamed: Driver L.1 (AO1), Driver L.2 (AO1), Driver L.11 (BO1), Driver L.12 (BO1), P4.1
unnamed: PROG.11, R5.2
unnamed: Q1.1 (D), R21.2, R22.2
unnamed: R11#2.1, U7.12 (KEY)
unnamed: R8.1, U7.11 (LED)
PWM_L: Driver L.15 (PWMB), Driver L.23 (PWMA), U1#2.44 (PA10)
PWM_R: Driver R.15 (PWMB), Driver R.23 (PWMA), U1#2.12 (PA0)
SENSOR1: GRUZIK3.0.14, R3#2.2, SENSOR.4, U1#2.62 (PB9)
SENSOR2: GRUZIK3.0.13, R15.2, SENSOR.5, U1#2.60 (PB7)
SENSOR3: GRUZIK3.0.12, R4#2.2, SENSOR.6, U1#2.59 (PB6)
SENSOR4: GRUZIK3.0.11, R16.2, SENSOR.7, U1#2.58 (PB5)
SENSOR5: GRUZIK3.0.10, R5#2.2, SENSOR.8, U1#2.57 (PB4)
SENSOR6: GRUZIK3.0.9, R17.2, SENSOR.9, U1#2.55 (PD2)
SENSOR7: GRUZIK3.0.8, R6#2.2, SENSOR.10, U1#2.54 (PC12)
SENSOR8: GRUZIK3.0.7, R18.2, SENSOR.11, U1#2.53 (PC11)
SENSOR9: GRUZIK3.0.6, R7#2.2, SENSOR.12, U1#2.52 (PC10)
SENSOR10: GRUZIK3.0.5, R19.2, SENSOR.13, U1#2.51 (PA15)
SENSOR11: GRUZIK3.0.4, R8#2.2, SENSOR.14, U1#2.18 (PA4)
SENSOR12: GRUZIK3.0.3, R20.2, SENSOR.15, U1#2.19 (PA5)
SPI2_CLK: SD_Card.5 (CLK), U1#2.35 (PB13)
SPI2_CS: SD_Card.2 (DAT3/CD), U1#2.34 (PB12)
SPI2_MISO: SD_Card.7 (DAT0), U1#2.36 (PB14)
SPI2_MOSI: SD_Card.3 (CMD), U1#2.37 (PB15)
SYS_JTCK_SWCLK: PROG.6, U1#2.50 (PA14)
SYS_JTDO_SWO: PROG.8, U1#2.56 (PB3)
SYS_JTMS_SWDIO: PROG.4, U1#2.49 (PA13)
VDC: +VIN-.1, C13#2.1, C18.1, C19.1, C23.1, C24.1, Driver L.13 (VM2), Driver L.14 (VM3), Driver L.24 (VM1), Driver R.13 (VM2), Driver R.14 (VM3), Driver R.24 (VM1), R4.2, U2.3 (VI)
VREF+: C2.1, C3.1, L1.1, U1#2.28 (VREF+), U1#2.29 (VDDA)

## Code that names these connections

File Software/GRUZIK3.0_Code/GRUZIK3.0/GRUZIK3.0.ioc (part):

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Mcu.Name=STM32G474R(B-C-E)Tx
Mcu.Package=LQFP64
Mcu.UserName=STM32G474RETx
PA0.GPIOParameters=GPIO_Label
PA0.GPIO_Label=PWM_R
PA0.Signal=S_TIM2_CH1
PA1.Mode=IN2-Single-Ended
PA1.Signal=ADC1_IN2
PA10.GPIOParameters=GPIO_Label
PA10.GPIO_Label=PWM_L
PA10.Signal=S_TIM2_CH4
PA11.GPIOParameters=GPIO_Label
PA11.GPIO_Label=ENCODER_L_1
PA11.Signal=S_TIM4_CH1
PA12.GPIOParameters=GPIO_Label
PA12.GPIO_Label=ENCODER_L_2
PA12.Signal=S_TIM4_CH2
PA13.GPIOParameters=GPIO_Label
PA13.GPIO_Label=T_SWDIO
PA13.Mode=Serial_Wire
PA13.Signal=SYS_JTMS-SWDIO
PA14.GPIOParameters=GPIO_Label
PA14.GPIO_Label=T_SWCLK
PA14.Mode=Serial_Wire
PA14.Signal=SYS_JTCK-SWCLK
PA15.GPIOParameters=GPIO_Label
PA15.GPIO_Label=SENSOR10
PA15.Signal=GPIO_Input
PA2.GPIOParameters=GPIO_Label
PA2.GPIO_Label=LPUART1_TX [STLINKV3E_VCP_RX]
PA2.Mode=Asynchronous
PA2.Signal=LPUART1_TX
PA3.GPIOParameters=GPIO_Label
PA3.GPIO_Label=LPUART1_RX [STLINKV3E_VCP_TX]
PA3.Mode=Asynchronous
PA3.Signal=LPUART1_RX
PA4.GPIOParameters=GPIO_Label
PA4.GPIO_Label=SENSOR11
PA4.Signal=GPIO_Input
PA5.GPIOParameters=GPIO_Label
PA5.GPIO_Label=SENSOR12
PA5.Signal=GPIO_Input
PA6.GPIOParameters=GPIO_Label
PA6.GPIO_Label=LED_4
PA6.Signal=GPIO_Output
PA7.GPIOParameters=GPIO_Label
PA7.GPIO_Label=LED_3
PA7.Signal=GPIO_Output
PA8.GPIOParameters=GPIO_Label
PA8.GPIO_Label=Motor_L_A
PA8.Signal=GPIO_Output
PA9.GPIOParameters=GPIO_Label
PA9.GPIO_Label=Motor_L_B
PA9.Signal=GPIO_Output
PB12.GPIOParameters=GPIO_Label
PB12.GPIO_Label=SPI2_CS
PB12.Signal=GPIO_Output
PB13.Mode=Full_Duplex_Master
PB13.Signal=SPI2_SCK
PB14.Mode=Full_Duplex_Master
PB14.Signal=SPI2_MISO
PB15.Mode=Full_Duplex_Master
PB15.Signal=SPI2_MOSI
PB3.GPIOParameters=GPIO_Label
PB3.GPIO_Label=T_SWO
PB3.Signal=SYS_JTDO-SWO
PB4.GPIOParameters=GPIO_Label
PB4.GPIO_Label=SENSOR5
PB4.Signal=GPIO_Input
PB5.GPIOParameters=GPIO_Label
PB5.GPIO_Label=SENSOR4
PB5.Signal=GPIO_Input
PB6.GPIOParameters=GPIO_Label
PB6.GPIO_Label=SENSOR3
PB6.Signal=GPIO_Input
PB7.GPIOParameters=GPIO_Label
PB7.GPIO_Label=SENSOR2
PB7.Signal=GPIO_Input
PB9.GPIOParameters=GPIO_Label
PB9.GPIO_Label=SENSOR1
PB9.Signal=GPIO_Input
PC0.GPIOParameters=GPIO_Label
PC0.GPIO_Label=ENCODER_R_1
PC0.Signal=S_TIM1_CH1
PC1.GPIOParameters=GPIO_Label
PC1.GPIO_Label=ENCODER_R_2
PC1.Signal=S_TIM1_CH2
PC10.GPIOParameters=GPIO_Label
PC10.GPIO_Label=SENSOR9
PC10.Signal=GPIO_Input
PC11.GPIOParameters=GPIO_Label
PC11.GPIO_Label=SENSOR8
PC11.Signal=GPIO_Input
PC12.GPIOParameters=GPIO_Label
PC12.GPIO_Label=SENSOR7
PC12.Signal=GPIO_Input
PC13.GPIOParameters=GPIO_Label
PC13.GPIO_Label=LEDON
PC13.Signal=GPIO_Output
PC14-OSC32_IN.Mode=LSE-External-Oscillator
PC14-OSC32_IN.Signal=RCC_OSC32_IN
PC15-OSC32_OUT.Mode=LSE-External-Oscillator
PC15-OSC32_OUT.Signal=RCC_OSC32_OUT
PC2.GPIOParameters=GPIO_Label
PC2.GPIO_Label=Motor_R_A
PC2.Signal=GPIO_Output
PC3.GPIOParameters=GPIO_Label
PC3.GPIO_Label=Motor_R_B
PC3.Signal=GPIO_Output
PC4.GPIOParameters=GPIO_Label
PC4.GPIO_Label=LED_2
PC4.Signal=GPIO_Output
PC5.GPIOParameters=GPIO_Label
PC5.GPIO_Label=LED_1
PC5.Signal=GPIO_Output
PC6.GPIOParameters=GPIO_Label
PC6.GPIO_Label=Motor_STBY
PC6.Signal=GPIO_Output
PC8.Mode=I2C
PC8.Signal=I2C3_SCL
PC9.Mode=I2C
PC9.Signal=I2C3_SDA
PD2.GPIOParameters=GPIO_Label
PD2.GPIO_Label=SENSOR6
PD2.Signal=GPIO_Input
PF0-OSC_IN.Mode=HSE-External-Oscillator
PF0-OSC_IN.Signal=RCC_OSC_IN
PF1-OSC_OUT.Mode=HSE-External-Oscillator
PF1-OSC_OUT.Signal=RCC_OSC_OUT
RCC.HSE_VALUE=24000000
RCC.SYSCLKFreq_VALUE=170000000
RCC.SYSCLKSource=RCC_SYSCLKSOURCE_PLLCLK
board=NUCLEO-G474RE
boardIOC=true

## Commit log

2024-12-21 v0.0.1
2025-01-19 v0.02
2025-02-24 Encoders Added
2025-03-03 Encoders Fixed :)
    PI motor speed controllers finally work as intended
2025-03-16 Initial maping done
2025-03-16 Maping with Encoders done
2025-03-16 maping done
2025-03-26 New motors and modes
2025-04-10 10.04.2025
2025-10-28 Software update
2025-11-04 Software Update Mapping
2026-05-16 before code renew
2026-05-16 new code
2026-05-16 mapping is working
2026-05-17 ready code
